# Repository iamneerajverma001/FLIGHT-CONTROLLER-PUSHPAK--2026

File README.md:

# Pushpak Flight Controller (FCV1)

[Download PCB ZIP](https://github.com/iamneerajverma001/FLIGHT-CONTROLLER-PUSHPAK--2026/archive/refs/heads/main.zip) · One-click download
[Open Portfolio App](https://cv6gnv.csb.app) · One-click interactive project summary

Quick links: [Visuals](#visuals) | [System overview](#system-overview) | [Core specs](#core-hardware-specifications) | [Block diagram](#block-diagram) | [Manufacturing](#manufacturing) | [Architecture](#architecture-deep-dive)

Pushpak FCV3 is a 36x36mm, 4-layer, noise-optimized flight controller built for high-performance FPV and autonomous payload delivery.

## Visuals
| Top view | Bottom view |
| --- | --- |
|  |  |

## System overview

## Key assets
| Asset | Location |
| --- | --- |
| KiCad project | [hardware/FCV3 project.kicad_pro](hardware/FCV3%20project.kicad_pro) |
| Architecture deep dive | [docs/HARDWARE_ARCHITECTURE.md](docs/HARDWARE_ARCHITECTURE.md) |
| System overview graphic | [docs/system_overview.png](docs/system_overview.png) |
| 3D model (VRML) | [outputs/FCV3 project.wrl](outputs/FCV3%20project.wrl) |
| Portfolio web app | [Open Portfolio App](https://cv6gnv.csb.app) |

## 3D model
- Board model (VRML): [outputs/FCV3 project.wrl](outputs/FCV3%20project.wrl)

## Block diagram
```mermaid
flowchart LR
  VBAT["LiPo VBAT"] --> BUCK["5V Sync Buck"]
  BUCK --> LDO["3.3V LDO"]
  LDO --> MCU["STM32F405"]
  MCU -->|SPI| IMU["ICM-42688-P"]
  MCU -->|I2C/SPI| BARO["BMP280 / BMP390"]
  MCU -->|SPI| FLASH["W25Q128"]
  MCU -->|Timers/DMA| ESC["4-in-1 ESC - DShot"]
  MCU -->|UART| GPS["GPS"]
  MCU -->|UART| RX["Radio Receiver"]
  MCU -->|CAN| CAN["DroneCAN"]
  MCU -->|USB| USBC["USB-C"]
  MCU -->|GPIO + BSS138| LED["WS2812B LEDs"]
```

## Core hardware specifications
- Processor: STM32F405RGT6 (ARM Cortex-M4) for high-speed calculation.
- IMU (Gyro): ICM-42688-P running on a dedicated ultra-fast SPI bus.
- Barometer: BMP280 / BMP390 for altitude hold.
- Blackbox: W25Q128 (16MB Flash) for flight data logging.
- Power delivery: High-efficiency 5V synchronous buck converter (MP1584 / TPS54202) taking raw LiPo voltage, paired with a clean 3.3V LDO for logic.

## Connectivity & I/O
- Motor control: 4-in-1 ESC connector (J21) with full hardware timer and DMA support for zero-latency DShot600.
- Expansions: DroneCAN telemetry, dedicated GPS port, and Radio Receiver port.
- Extras: WS2812B LED output (via BSS138 5V logic shifter) and USB-C for configuration.

## Repository navigation & usage
- hardware/ - KiCad project, schematic, PCB, and library tables.
- libraries/ - Custom symbols, footprints, and 3D models.
- outputs/ - BOM, reports, and manufacturing/export files.
- images/ - Board renders and screenshots.
- docs/ - Deep-dive design notes.

## How to open
1. Clone the repository.
2. Open [hardware/FCV3 project.kicad_pro](hardware/FCV3%20project.kicad_pro) in KiCad 8.0.

## Outputs
- BOM: [outputs/FCV3 project.csv](outputs/FCV3%20project.csv)
- ERC report: [outputs/ERC.rpt](outputs/ERC.rpt)
- Design report: [outputs/report.txt](outputs/report.txt)

## Manufacturing
Fabrication exports (Gerbers and Pick & Place/CPL) can be generated into outputs/ when you are ready to manufacture.

## Architecture deep dive
See the design intent and layout strategy in [docs/HARDWARE_ARCHITECTURE.md](docs/HARDWARE_ARCHITECTURE.md).

## Pinout quick view
For the full pinout tables, see [docs/HARDWARE_ARCHITECTURE.md](docs/HARDWARE_ARCHITECTURE.md).

### Core sensors and buses
| Feature | MCU Pin | Bus | Component |
| --- | --- | --- | --- |
| Gyro CS | PA4 | SPI1 | ICM-42688-P |
| Gyro SCK | PA5 | SPI1 | ICM-42688-P |
| Gyro MISO | PA6 | SPI1 | ICM-42688-P |
| Gyro MOSI | PA7 | SPI1 | ICM-42688-P |
| Flash CS | PA15 | SPI3 | W25Q128 |
| Flash SCK | PC10 | SPI3 | W25Q128 |
| Flash MISO | PC11 | SPI3 | W25Q128 |
| Flash MOSI | PC12 | SPI3 | W25Q128 |
| Baro SCL | PA8 | I2C3 | BMP280 / BMP390 |
| Baro SDA | PC9 | I2C3 | BMP280 / BMP390 |

### Motor and payload outputs
| Output | MCU Pin | Timer | Connection |
| --- | --- | --- | --- |
| Motor 1 | PB3 | TIM2_CH2 | J21 ESC port |
| Motor 2 | PB10 | TIM2_CH3 | J21 ESC port |
| Motor 3 | PB2 | TIM2_CH4 | J21 ESC port |
| Motor 4 | PB4 | TIM3_CH1 | J21 ESC port |
| Motor 5 | PB0 | TIM3_CH3 | Expansion |
| Motor 6 | PB14 | TIM12_CH1 | Expansion |
| Servo 1 | PB15 | TIM12_CH2 | Payload / gimbal |

## Challenges & learnings
- Stackup discipline and clean partitioning were critical to keeping gyro noise low.
- Layout geometry matters as much as routing for flight stability.
- Tight power loops and ground shielding reduced EMI from the buck stage.

## License
Project files are licensed under [LICENSE](LICENSE).
Library components are provided under the terms in [license.txt](license.txt).

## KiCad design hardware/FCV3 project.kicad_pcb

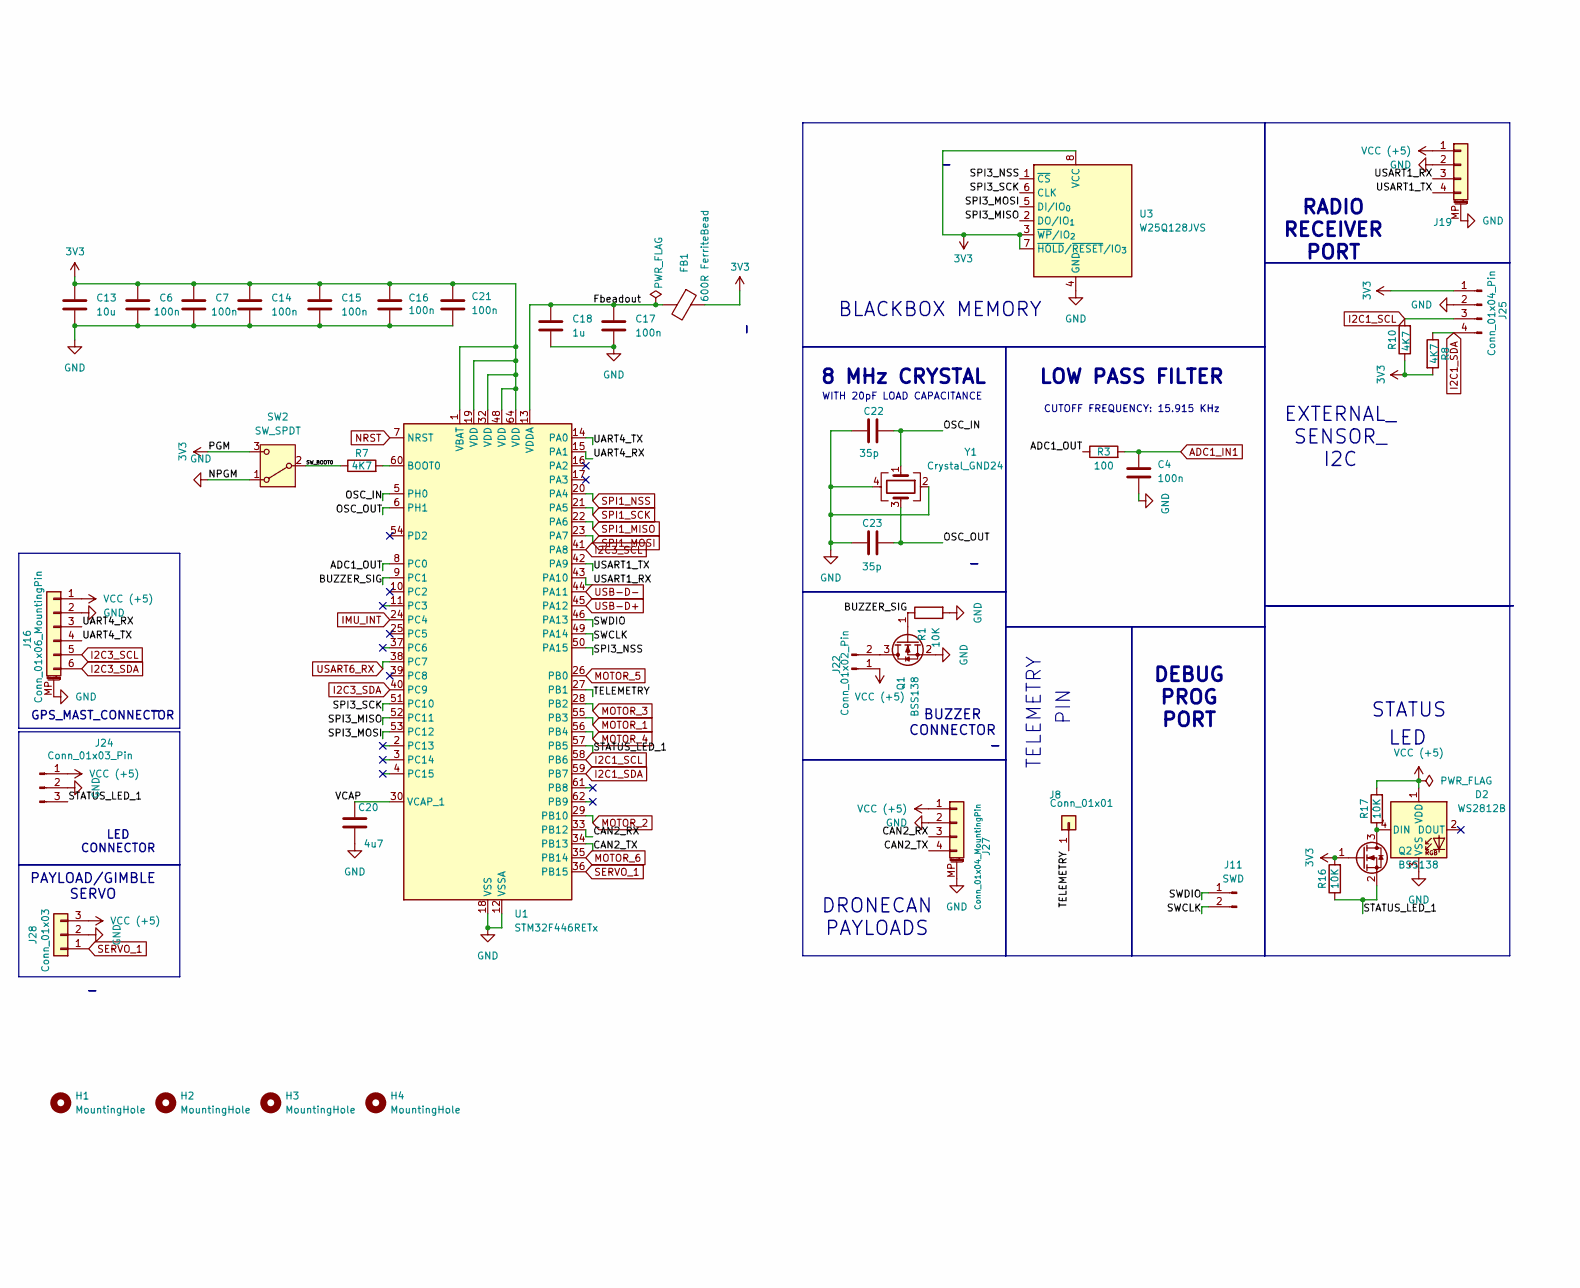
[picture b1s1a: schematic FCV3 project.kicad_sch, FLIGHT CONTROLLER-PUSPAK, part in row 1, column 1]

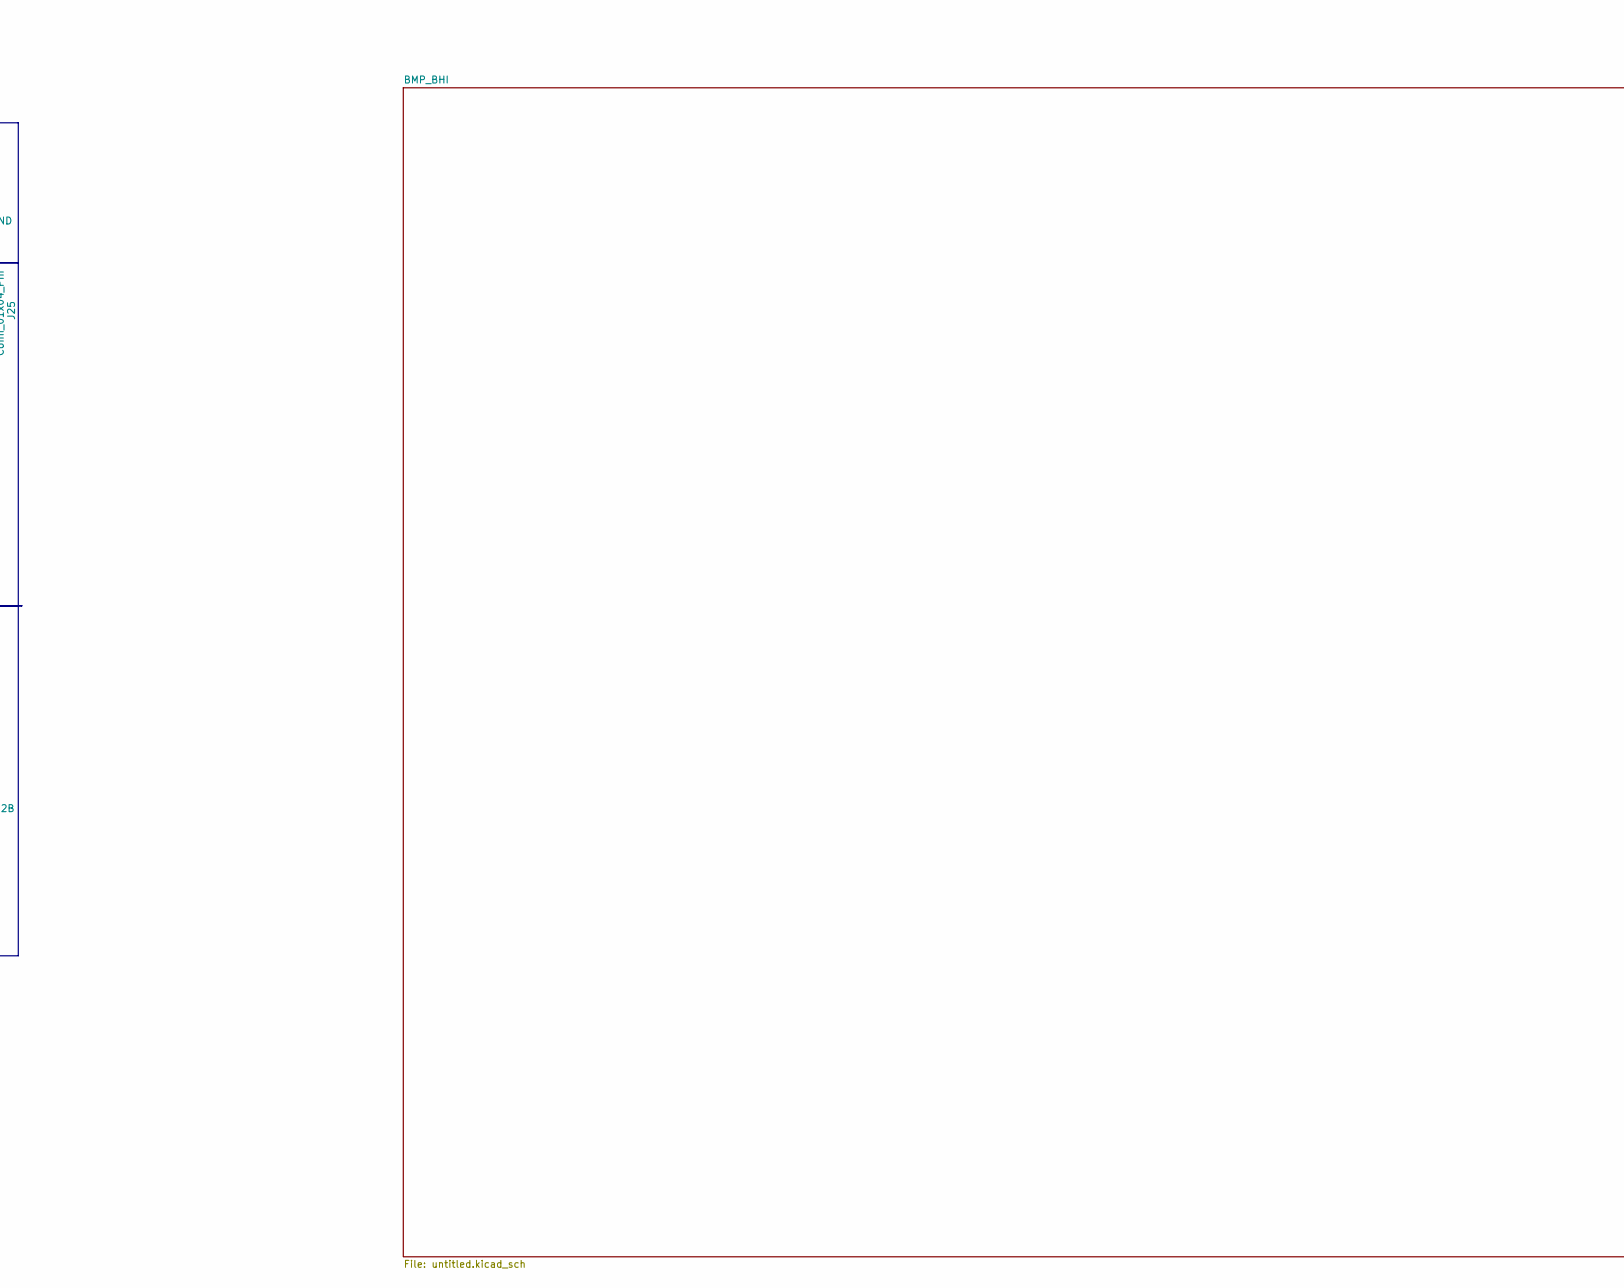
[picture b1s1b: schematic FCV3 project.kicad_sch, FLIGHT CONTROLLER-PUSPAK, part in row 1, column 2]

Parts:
C4, C6, C7, C14, C15, C16, C17, C21: 100n; C_0402_1005Metric
C13: 10u; C_0603_1608Metric
C18: 1u; C_0402_1005Metric
C20: 4u7; C_0603_1608Metric
C22, C23: 35p; C_0402_1005Metric
D2: WS2812B; LED_WS2812B_PLCC4_5.0x5.0mm_P3.2mm
FB1: 600R FerriteBead; L_0603_1608Metric
H1, H2, H3, H4: MountingHole; MountingHole_2.2mm_M2
J8: Conn_01x01; PinHeader_1x01_P2.54mm_Vertical
J11: SWD; PinSocket_1x02_P2.54mm_Vertical
J16: Conn_01x06_MountingPin; JST_SH_SM06B-SRSS-TB_1x06-1MP_P1.00mm_Horizontal
J19: RADIO; JST_SH_BM04B-SRSS-TB_1x04-1MP_P1.00mm_Vertical
J22: Conn_01x02_Pin; PinHeader_1x02_P2.54mm_Vertical
J24: Conn_01x03_Pin; PinHeader_1x03_P2.54mm_Vertical
J25: Conn_01x04_Pin; PinHeader_1x04_P2.54mm_Vertical
J27: Conn_01x04_MountingPin; JST_SH_SM04B-SRSS-TB_1x04-1MP_P1.00mm_Horizontal
J28: Conn_01x03; PinHeader_1x03_P2.54mm_Vertical
Q1, Q2: BSS138; SOT-23
R1, R16, R17: 10K; R_0402_1005Metric
R3: 100; R_0402_1005Metric
R7, R8, R10: 4K7; R_0402_1005Metric
SW2: SW_SPDT; SW_SPDT_PCM12
U1: STM32F446RETx; LQFP-64_10x10mm_P0.5mm
U3: W25Q128JVS; SOIC-8_5.3x5.3mm_P1.27mm
Y1: Crystal_GND24; Crystal_SMD_3225-4Pin_3.2x2.5mm

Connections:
3V3: C6.1, C7.1, C13.1, C14.1, C15.1, C16.1, C21.2, FB1.1, J25.1, Q2.1 (G), R8.2, R10.1, R16.2, SW2.3 (C), U1.1 (VBAT), U1.19 (VDD), U1.32 (VDD), U1.48 (VDD), U1.64 (VDD), U3.3 (~WP/IO_{2}), U3.7 (~HOLD/~RESET/IO_{3}), U3.8 (VCC); also elsewhere on the board
/ADC1_OUT: R3.1, U1.8 (PC0)
/BUZZER_SIG: Q1.1 (G), R1.1, U1.9 (PC1)
/CAN2_RX: J27.3, U1.33 (PB12)
/CAN2_TX: J27.4, U1.34 (PB13)
/Fbeadout: C17.1, C18.1, FB1.2, U1.13 (VDDA)
/OSC_IN: C22.1, U1.5 (PH0), Y1.1
/OSC_OUT: C23.1, U1.6 (PH1), Y1.3
/SPI3_MISO: U1.52 (PC11), U3.2 (DO/IO_{1})
/SPI3_MOSI: U1.53 (PC12), U3.5 (DI/IO_{0})
/SPI3_NSS: U1.50 (PA15), U3.1 (~CS)
/SPI3_SCK: U1.51 (PC10), U3.6 (CLK)
/STATUS_LED_1: J24.3, Q2.2 (S), R16.1, U1.57 (PB5)
/SWCLK: J11.2, U1.49 (PA14)
/SWDIO: J11.1, U1.46 (PA13)
/SW_BOOT0: R7.1, SW2.2 (B)
/TELEMETRY: J8.1 (Pin_1_1), U1.27 (PB1)
/UART4_RX: J16.3, U1.15 (PA1)
/UART4_TX: J16.4, U1.14 (PA0)
/USART1_RX: J19.3, U1.43 (PA10)
/USART1_TX: J19.4, U1.42 (PA9)
/VCAP: C20.1, U1.30 (VCAP_1)
ADC1_IN1: C4.2, R3.2
GND: C4.1, C6.2, C7.2, C13.2, C14.2, C15.2, C16.2, C17.2, C18.2, C20.2, C21.1, C22.2, C23.2, D2.3 (VSS), J16.2, J16.MP (MountPin), J19.2, J19.MP (MountPin), J24.2, J25.2, J27.2, J27.MP (MountPin), J28.2, Q1.2 (S), R1.2, SW2.1 (A), U1.12 (VSSA), U1.18 (VSS), U1.31 (VSS), U1.47 (VSS), U1.63 (VSS), U3.4 (GND), Y1.2, Y1.4; also elsewhere on the board
I2C1_SCL: J25.3, R10.2, U1.58 (PB6)
I2C1_SDA: J25.4, R8.1, U1.59 (PB7)
I2C3_SCL: J16.5, U1.41 (PA8); also elsewhere on the board
I2C3_SDA: J16.6, U1.40 (PC9); also elsewhere on the board
IMU_INT: U1.24 (PC4); also elsewhere on the board
MOTOR_1: U1.55 (PB3); also elsewhere on the board
MOTOR_2: U1.29 (PB10); also elsewhere on the board
MOTOR_3: U1.28 (PB2); also elsewhere on the board
MOTOR_4: U1.56 (PB4); also elsewhere on the board
MOTOR_5: U1.26 (PB0); also elsewhere on the board
MOTOR_6: U1.35 (PB14); also elsewhere on the board
NRST: U1.7 (NRST); also elsewhere on the board
unnamed: D2.4 (DIN), Q2.3 (D), R17.1
unnamed: J22.2, Q1.3 (D)
unnamed: R7.2, U1.60 (BOOT0)
SERVO_1: J28.1, U1.36 (PB15)
SPI1_MISO: U1.22 (PA6); also elsewhere on the board
SPI1_MOSI: U1.23 (PA7); also elsewhere on the board
SPI1_NSS: U1.20 (PA4); also elsewhere on the board
SPI1_SCK: U1.21 (PA5); also elsewhere on the board
USART6_RX: U1.38 (PC7); also elsewhere on the board
USB-D+: U1.45 (PA12); also elsewhere on the board
USB-D-: U1.44 (PA11); also elsewhere on the board
VCC (+5): D2.1 (VDD), J16.1, J19.1, J22.1, J24.1, J27.1, J28.3, R17.2; also elsewhere on the board

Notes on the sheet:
PAYLOAD/GIMBLE SERVO
RADIO RECEIVER PORT
LED
BLACKBOX MEMORY
GPS_MAST_CONNECTOR
EXTERNAL_ SENSOR_ I2C
CUTOFF FREQUENCY: 15.915 KHz
LOW PASS FILTER
PIN
DRONECAN PAYLOADS
TELEMETRY
LED CONNECTOR
DEBUG PROG PORT
8 MHz CRYSTAL
STATUS
WITH 20pF LOAD CAPACITANCE
BUZZER CONNECTOR

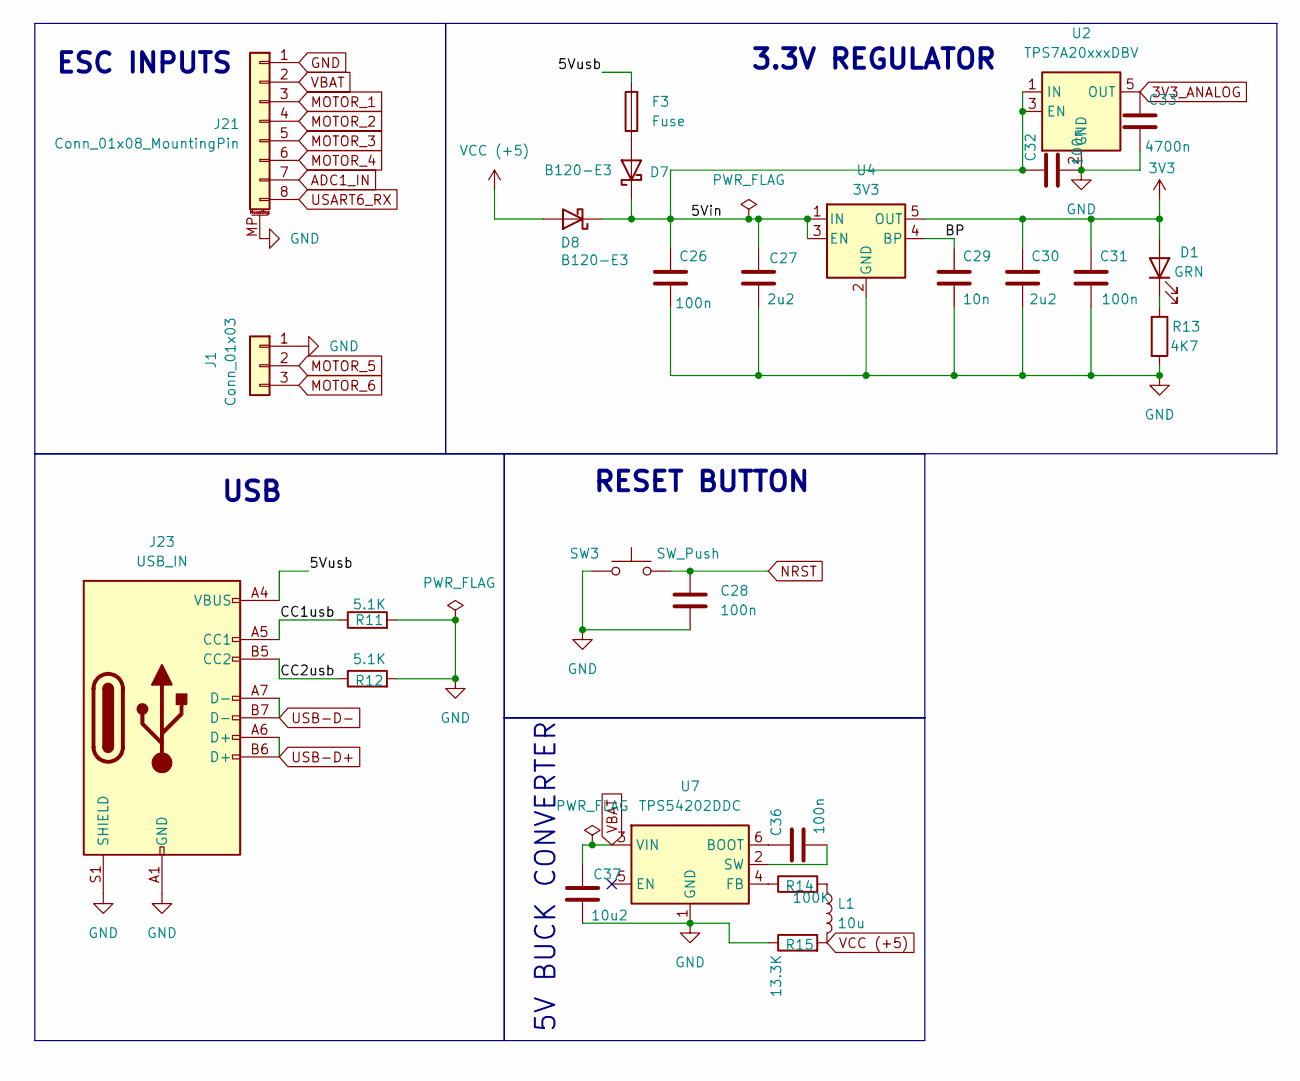
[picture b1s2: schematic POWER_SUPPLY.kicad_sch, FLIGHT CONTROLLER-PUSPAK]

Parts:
C26, C28, C31, C32, C36: 100n; C_0402_1005Metric
C27, C30: 2u2; C_0603_1608Metric
C29: 10n; C_0402_1005Metric
C33: 4700n; C_0402_1005Metric
C37: 10u2; C_0603_1608Metric
D1: GRN; LED_0603_1608Metric
D7, D8: B120-E3; D_0603_1608Metric
F3: Fuse; Fuse_1206_3216Metric
J1: Conn_01x03; PinHeader_1x03_P2.54mm_Vertical
J21: Conn_01x08_MountingPin; JST_SH_BM08B-SRSS-TB_1x08-1MP_P1.00mm_Vertical
J23: USB_IN; USB_C_Receptacle_GCT_USB4105-xx-A_16P_TopMnt_Horizontal
L1: 10u; L_APV_ANR252012
R11, R12: 5.1K; R_0402_1005Metric
R13: 4K7; R_0402_1005Metric
R14: 100K; R_0402_1005Metric
R15: 13.3K; R_0402_1005Metric
SW3: SW_Push; SW_Push_1TS009xxxx-xxxx-xxxx_6x6x5mm
U2: TPS7A20xxxDBV; SOT-23-5
U4: 3V3; SOT-23-5
U7: TPS54202DDC; SOT-23-6

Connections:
3V3: C30.1, C31.1, D1.2 (A), U4.5 (OUT); also elsewhere on the board
3V3_ANALOG: C33.1, U2.5 (OUT); also elsewhere on the board
/POWER SUPPLY/5Vin: C26.1, C27.1, C32.1, D7.1 (K), D8.1 (K), U2.1 (IN), U2.3 (EN), U4.1 (IN), U4.3 (EN)
/POWER SUPPLY/5Vusb: F3.2, J23.A4 (VBUS), J23.A9 (VBUS), J23.B4 (VBUS), J23.B9 (VBUS)
/POWER SUPPLY/BP: C29.1, U4.4 (BP)
/POWER SUPPLY/CC1usb: J23.A5 (CC1), R11.1
/POWER SUPPLY/CC2usb: J23.B5 (CC2), R12.1
ADC1_IN: J21.7
GND: C26.2, C27.2, C28.2, C29.2, C30.2, C31.2, C32.2, C33.2, C37.2, J1.1, J21.1, J21.MP (MountPin), J23.A1 (GND), J23.A12 (GND), J23.B1 (GND), J23.B12 (GND), J23.S1 (SHIELD), R11.2, R12.2, R13.2, R15.1, SW3.1, U2.2 (GND), U4.2 (GND), U7.1 (GND); also elsewhere on the board
MOTOR_1: J21.3; also elsewhere on the board
MOTOR_2: J21.4; also elsewhere on the board
MOTOR_3: J21.5; also elsewhere on the board
MOTOR_4: J21.6; also elsewhere on the board
MOTOR_5: J1.2; also elsewhere on the board
MOTOR_6: J1.3; also elsewhere on the board
NRST: C28.1, SW3.2; also elsewhere on the board
unnamed: D1.1 (K), R13.1
unnamed: D7.2 (A), F3.1
unnamed: L1.1, R14.2
unnamed: C36.1, U7.6 (BOOT)
unnamed: R14.1, U7.4 (FB)
unnamed: C36.2, U7.2 (SW)
USART6_RX: J21.8; also elsewhere on the board
USB-D+: J23.A6 (D+), J23.B6 (D+); also elsewhere on the board
USB-D-: J23.A7 (D-), J23.B7 (D-); also elsewhere on the board
VBAT: C37.1, J21.2, U7.3 (VIN)
VCC (+5): D8.2 (A), L1.2, R15.2; also elsewhere on the board

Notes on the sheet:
USB
RESET BUTTON
ESC INPUTS
5V BUCK CONVERTER
3.3V REGULATOR

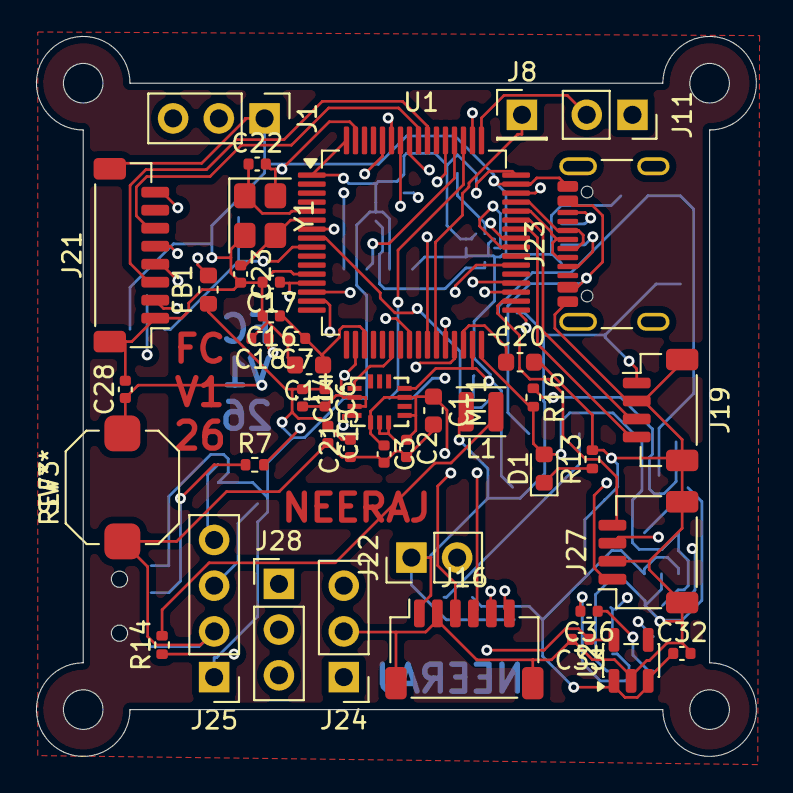
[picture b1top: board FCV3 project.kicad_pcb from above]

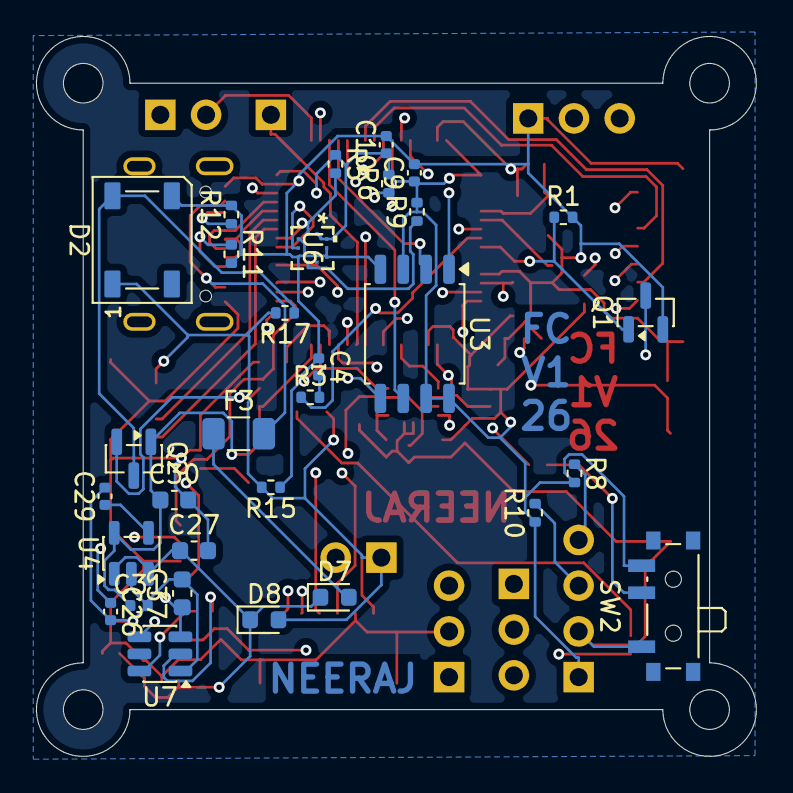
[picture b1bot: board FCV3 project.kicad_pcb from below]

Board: 4 copper layers, 40.0 x 40.0 mm, 78 parts (31 on the bottom side), 62 nets.

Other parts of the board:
C1: 2u2; C_0603_1608Metric
C2, C9, C10: 100n; C_0402_1005Metric
C3: 10n; C_0402_1005Metric
MT1: ICM-42688-P; LGA-14_L3.0-W2.5-P0.50-BL
R5, R6: 4K7; R_0402_1005Metric
R9: 100K; R_0402_1005Metric
U6: BMP390; 10LGA_2X2X0p75_BOS-L

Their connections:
3V3: C9.1, C10.1, R5.1, R6.2, R9.2, U6.1 (VDDIO), U6.10 (VDD); also elsewhere on the board
3V3_ANALOG: C1.1, C2.1, C3.1, MT1.5 (VDDIO), MT1.8 (VDD), MT1.10 (RESV__2); also elsewhere on the board
GND: C1.2, C2.2, C3.2, C9.2, C10.2, MT1.2 (RESV), MT1.3 (RESV__1), MT1.6 (GND), MT1.7 (FSYNC), MT1.11 (RESV__3), U6.3 (VSS), U6.5 (SDO), U6.8 (VSS), U6.9 (VSS); also elsewhere on the board
I2C3_SCL: R5.2, U6.2 (SCK); also elsewhere on the board
I2C3_SDA: R6.1, U6.4 (SDI); also elsewhere on the board
IMU_INT: MT1.4 (INT1/INT); also elsewhere on the board
unnamed: R9.1, U6.6 (CSB)
SPI1_MISO: MT1.1 (AP_SDO/AP_AD0); also elsewhere on the board
SPI1_MOSI: MT1.14 (AP_SDA/AP_SDIO/AP_SDI); also elsewhere on the board
SPI1_NSS: MT1.12 (AP_CS); also elsewhere on the board
SPI1_SCK: MT1.13 (AP_SCL/AP_SCLK); also elsewhere on the board

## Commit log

2026-05-27 Add ZIP download link
2026-05-27 Update portfolio URL
2026-05-27 Update board renders

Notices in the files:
README.md:
License: SamacSys
